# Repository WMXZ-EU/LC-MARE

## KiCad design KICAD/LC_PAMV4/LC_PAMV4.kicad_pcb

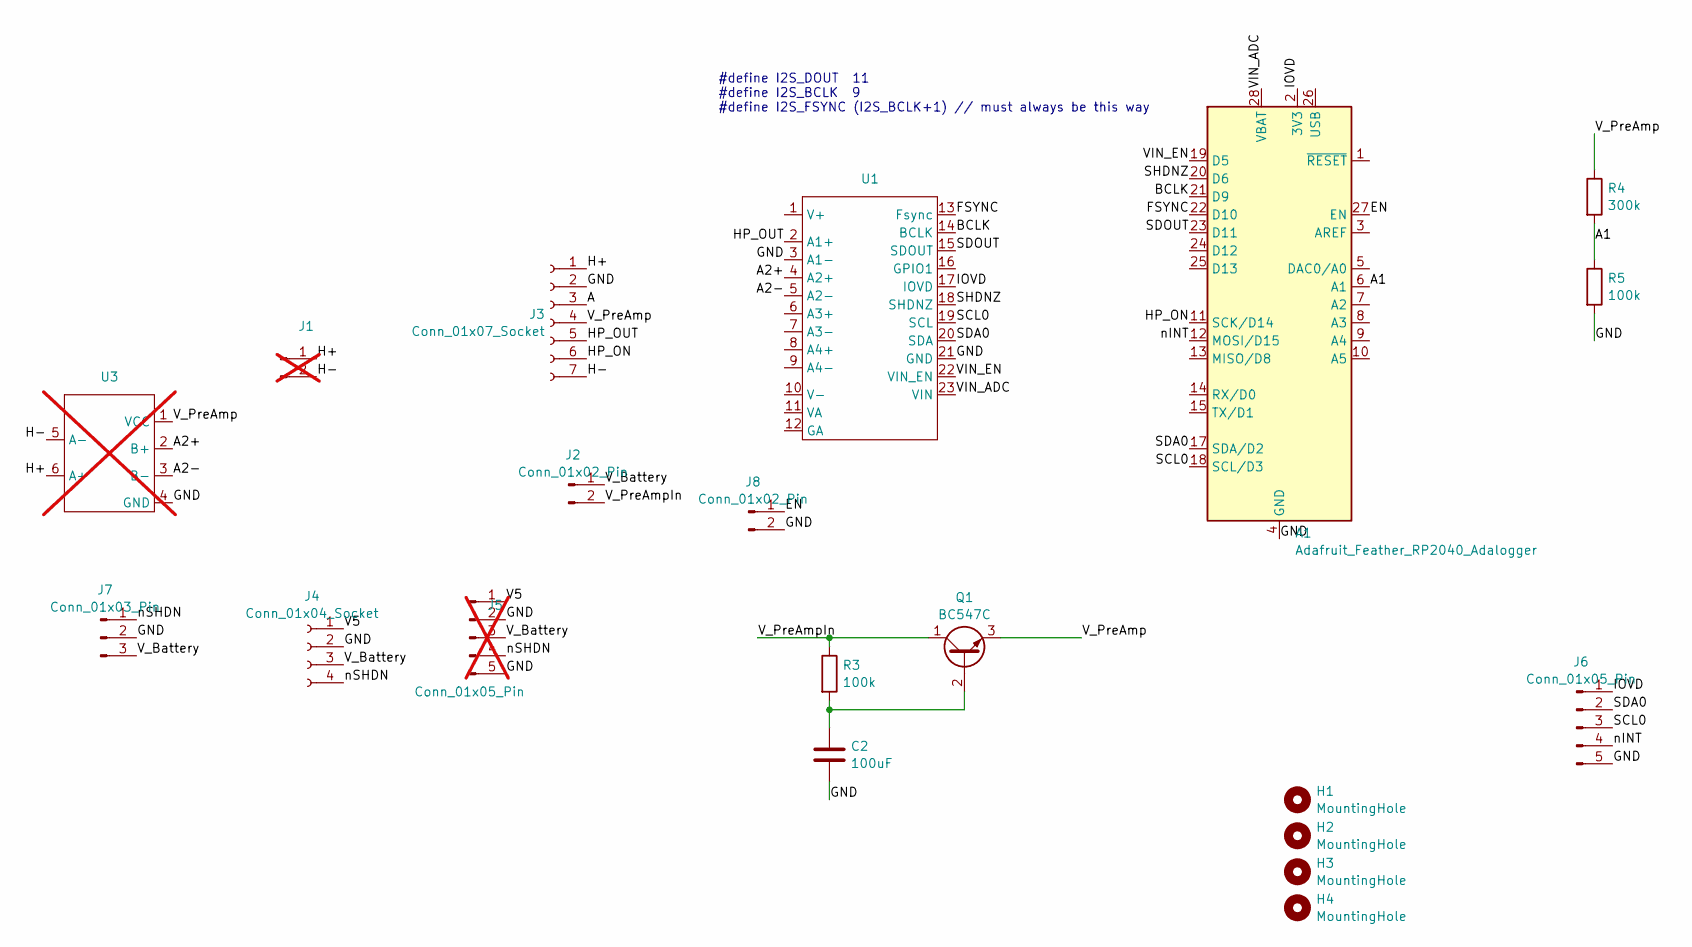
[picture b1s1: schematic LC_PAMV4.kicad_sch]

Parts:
A1: Adafruit_Feather_RP2040_Adalogger; Adafruit_Feather_WithMountingHoles
C2: 100uF; CP_Radial_D4.0mm_P2.00mm
H1, H2, H3, H4: MountingHole; MountingHole_3.2mm_M3_DIN965
J1: Conn_01x02_Male; Molex_PicoBlade_53048-0210_1x02_P1.25mm_Horizontal; not fitted
J2, J8: Conn_01x02_Pin; PinHeader_1x02_P2.54mm_Vertical
J3: Conn_01x07_Socket; HPAB
J4: Conn_01x04_Socket; PinHeader_1x04_P2.54mm_Vertical
J5: Conn_01x05_Pin; PinHeader_1x05_P2.54mm_Vertical; not fitted
J6: Conn_01x05_Pin; PinHeader_1x05_P2.54mm_Vertical
J7: Conn_01x03_Pin; PinHeader_1x03_P2.54mm_Vertical
Q1: BC547C; TO-92_Inline
R3, R5: 100k; R_Axial_DIN0204_L3.6mm_D1.6mm_P1.90mm_Vertical
R4: 300k; R_Axial_DIN0204_L3.6mm_D1.6mm_P1.90mm_Vertical
U1: ADC_V2
U3: Preamp-FET; not fitted

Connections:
/A: J3.3
/A1: A1.6 (A1), R4.2, R5.1
/A2+: U1.4 (A2+), U3.2 (B+)
/A2-: U1.5 (A2-), U3.3 (B-)
/BCLK: A1.21 (D9), U1.14 (BCLK)
/EN: A1.27 (EN), J8.1
/FSYNC: A1.22 (D10), U1.13 (Fsync)
/GND: A1.4 (GND), A1.16 (GND), C2.2, J3.2, J4.2, J5.2, J5.5, J6.5, J7.2, J8.2, R5.2, U1.3 (A1-), U1.21 (GND), U3.4 (GND)
/H+: J1.1, J3.1, U3.6 (A+)
/H-: J1.2, J3.7, U3.5 (A-)
/HP_ON: A1.11 (SCK/D24), J3.6
/HP_OUT: J3.5, U1.2 (A1+)
/IOVD: A1.2 (3V3), J6.1, U1.17 (IOVD)
/SCL0: A1.18 (SCL/D21), J6.3, U1.19 (SCL)
/SDA0: A1.17 (SDA/D20), J6.2, U1.20 (SDA)
/SDOUT: A1.23 (D11), U1.15 (SDOUT)
/SHDNZ: A1.20 (D6), U1.18 (SHDNZ)
/V5: J4.1, J5.1
/VIN_ADC: A1.28 (VBAT), U1.23 (VIN)
/VIN_EN: A1.19 (D5), U1.22 (VIN_EN)
/V_Battery: J2.1, J4.3, J5.3, J7.3
/V_PreAmp: J3.4, Q1.3 (E), R4.1, U3.1 (VCC)
/V_PreAmpIn: J2.2, Q1.1 (C), R3.1
/nINT: A1.12 (MOSI/D23), J6.4
/nSHDN: J4.4, J5.4, J7.1
unnamed: C2.1, Q1.2 (B), R3.2

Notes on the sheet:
#define I2S_DOUT 11 #define I2S_BCLK 9 #define I2S_FSYNC (I2S_BCLK+1) // must always be this way

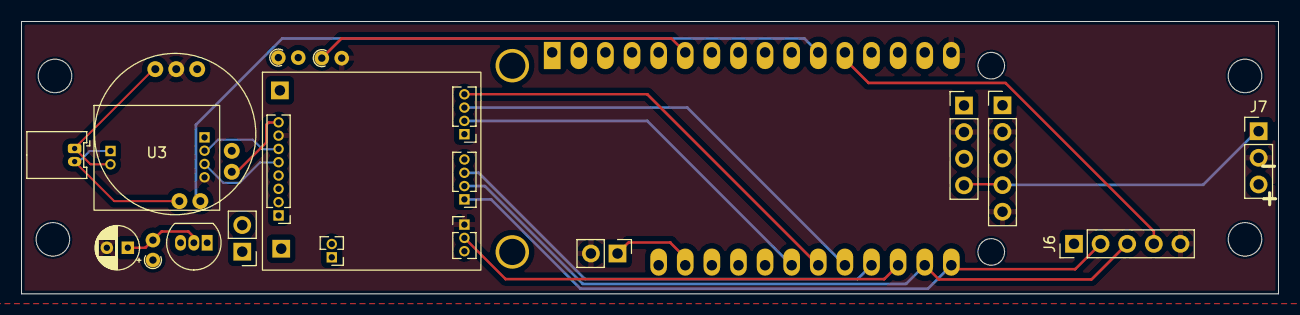
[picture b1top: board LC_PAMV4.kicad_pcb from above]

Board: 4 copper layers, 120.0 x 26.0 mm, 20 parts (1 on the bottom side), 25 nets.

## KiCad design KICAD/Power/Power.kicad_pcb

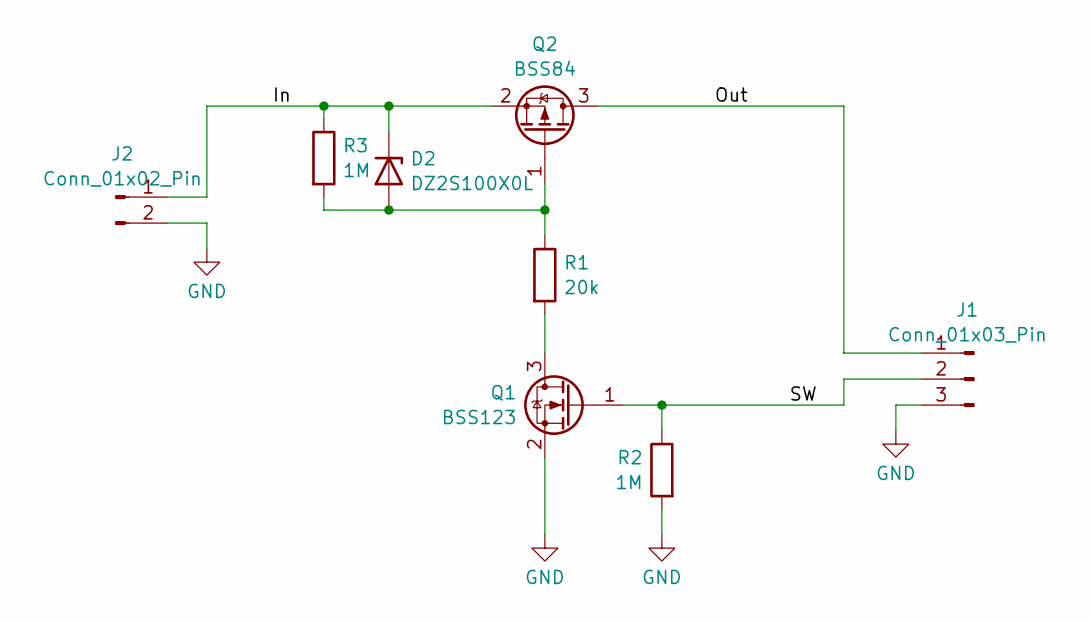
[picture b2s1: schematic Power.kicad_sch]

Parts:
D2: DZ2S100X0L; D_SOD-523
J1: Conn_01x03_Pin; PinHeader_1x03_P2.54mm_Vertical
J2: Conn_01x02_Pin; PinHeader_1x02_P2.54mm_Vertical
Q1: BSS123; SOT-23
Q2: BSS84; SOT-23
R1: 20k; R_0603_1608Metric
R2, R3: 1M; R_0603_1608Metric

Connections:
/In: D2.1 (K), J2.1, Q2.2 (S), R3.1
/Out: J1.1, Q2.3 (D)
/SW: J1.2, Q1.1 (G), R2.1
GND: J1.3, J2.2, Q1.2 (S), R2.2
unnamed: D2.2 (A), Q2.1 (G), R1.1, R3.2
unnamed: Q1.3 (D), R1.2

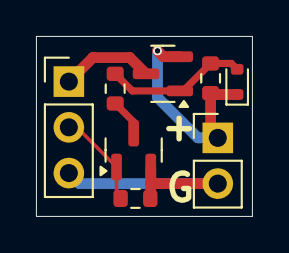
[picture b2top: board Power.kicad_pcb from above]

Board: 2 copper layers, 12.0 x 10.0 mm, 8 parts (0 on the bottom side), 6 nets.

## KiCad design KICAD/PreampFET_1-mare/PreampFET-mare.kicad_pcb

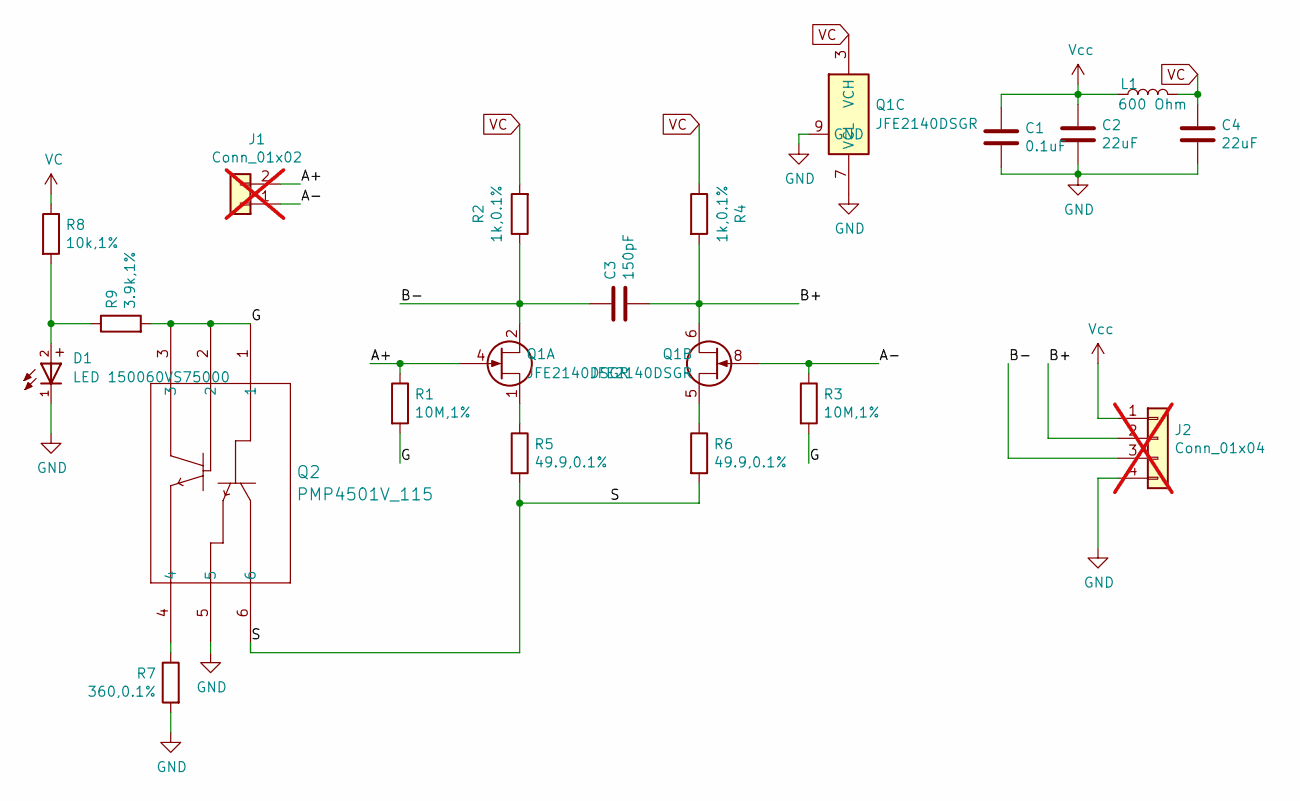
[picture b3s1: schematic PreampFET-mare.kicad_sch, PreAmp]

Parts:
C1: 0.1uF; C_0402_1005Metric
C2, C4: 22uF; C_0603_1608Metric
C3: 150pF; C_0402_1005Metric
D1: LED 150060VS75000; WL-SMCW_0603
J1: Conn_01x02; PinHeader_1x02_P1.27mm_Vertical; not fitted
J2: Conn_01x04; PinHeader_1x04_P1.27mm_Vertical; not fitted
L1: 600 Ohm; L_0603_1608Metric
Q1: JFE2140DSGR; WSON-8-1EP_2x2mm_P0.5mm_EP0.9x1.6mm_ThermalVias
Q2: PMP4501V_115; SOT666_NEX
R1, R3: 10M,1%; R_0402_1005Metric
R2, R4: 1k,0.1%; R_0402_1005Metric
R5, R6: 49.9,0.1%; R_0402_1005Metric
R7: 360,0.1%; R_0402_1005Metric
R8: 10k,1%; R_0402_1005Metric
R9: 3.9k,1%; R_0402_1005Metric

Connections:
/A+: J1.2, Q1.4, R1.1
/A-: J1.1, Q1.8, R3.1
/B+: C3.2, J2.2, Q1.6, R4.2
/B-: C3.1, J2.3, Q1.2, R2.1
/G: Q2.1, Q2.2, Q2.3, R1.2, R3.2, R9.2
/S: Q2.6, R5.2, R6.2
GND: C1.2, C2.2, C4.2, D1.1, J2.4, Q1.7 (VCL), Q1.9 (GND), Q2.5, R7.2
unnamed: D1.2, R8.2, R9.1
unnamed: Q1.1, R5.1
unnamed: Q1.5, R6.1
unnamed: Q2.4, R7.1
VC: C4.1, L1.2, Q1.3 (VCH), R2.2, R4.1, R8.1
Vcc: C1.1, C2.1, J2.1, L1.1

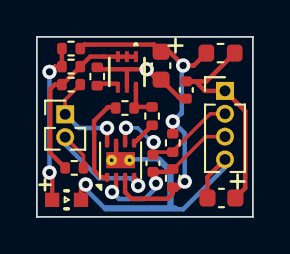
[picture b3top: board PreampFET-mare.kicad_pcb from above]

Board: 2 copper layers, 12.0 x 10.0 mm, 19 parts (0 on the bottom side), 13 nets.

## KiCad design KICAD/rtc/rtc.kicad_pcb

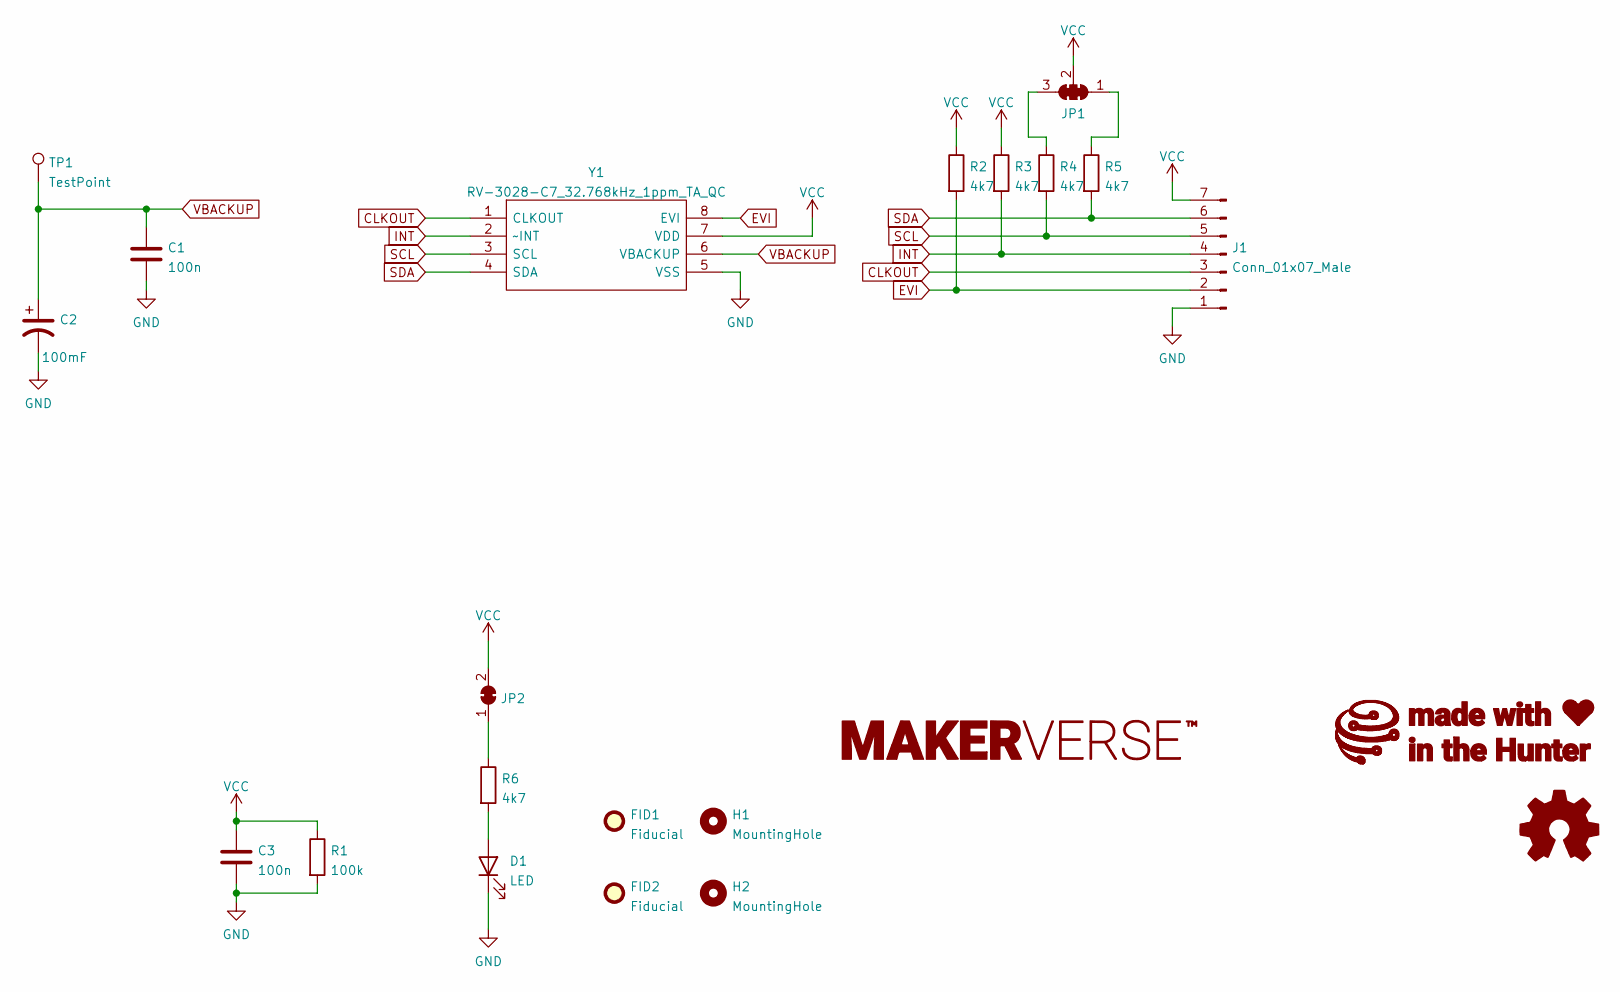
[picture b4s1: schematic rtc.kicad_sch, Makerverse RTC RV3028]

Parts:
C1, C3: 100n; C_0402_1005Metric
C2: 100mF; FC_10.5X5.5_
D1: LED; LED_0603_1608Metric
FID1, FID2: Fiducial; Fiducial_1mm_Mask2mm
H1, H2: MountingHole; MountingHole_3.2mm_M3
J1: Conn_01x07_Male; PinSocket_1x07_P2.54mm_Vertical
JP1: SolderJumper_3_Bridged123; SolderJumper-3_P1.3mm_Closed_RoundedPad1.0x1.5mm
JP2: SolderJumper_2_Bridged; SolderJumper-2_P1.3mm_Bridged_RoundedPad1.0x1.5mm
R1: 100k; R_0402_1005Metric
R2, R3, R4, R5, R6: 4k7; R_0402_1005Metric
TP1: TestPoint; TestPoint_THTPad_D1.5mm_Drill0.7mm
Y1: RV-3028-C7_32.768kHz_1ppm_TA_QC; RV3028C732768kHz1ppmTAQC; Mouser Part Number 428-203591-MG01

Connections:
CLKOUT: J1.3, Y1.1 (CLKOUT)
EVI: J1.2, R2.2, Y1.8 (EVI)
GND: C1.2, C2.2, C3.2, D1.1 (K), J1.1, R1.2, Y1.5 (VSS)
INT: J1.4, R3.2, Y1.2 (~INT)
unnamed: D1.2 (A), R6.2
unnamed: JP1.1 (A), R5.1
unnamed: JP1.3 (B), R4.1
unnamed: JP2.1 (A), R6.1
SCL: J1.5, R4.2, Y1.3 (SCL)
SDA: J1.6, R5.2, Y1.4 (SDA)
VBACKUP: C1.1, C2.1, TP1.1, Y1.6 (VBACKUP)
VCC: C3.1, J1.7, JP1.2 (C), JP2.2 (B), R1.1, R2.1, R3.1, Y1.7 (VDD)

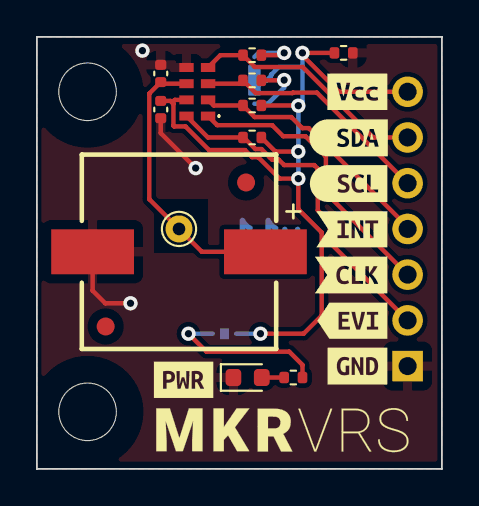
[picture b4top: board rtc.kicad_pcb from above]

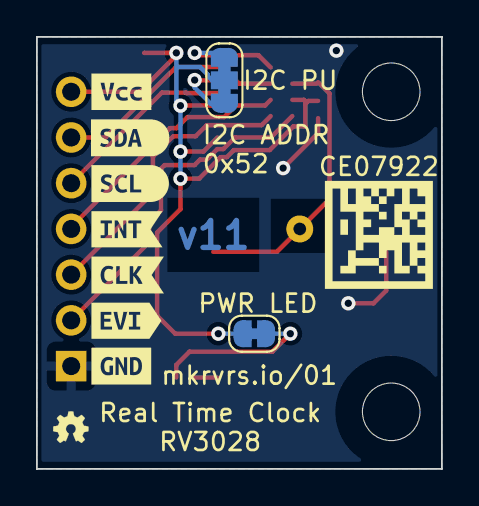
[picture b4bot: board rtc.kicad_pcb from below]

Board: 2 copper layers, 22.5 x 24.0 mm, 35 parts (9 on the bottom side), 12 nets.

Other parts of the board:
G1: LOGO; makerverse_logo_short_14.0x2.4mm
kibuzzard-610A0DD3: G***; kibuzzard-610A0DD3
kibuzzard-611F2ECA: G***; kibuzzard-611F2ECA
kibuzzard-611F2EE3: G***; kibuzzard-611F2EE3
kibuzzard-611F2EF5: G***; kibuzzard-611F2EF5
kibuzzard-611F2F08: G***; kibuzzard-611F2F08
kibuzzard-611F2F8F: G***; kibuzzard-611F2F8F
kibuzzard-611F2F9E: G***; kibuzzard-611F2F9E
kibuzzard-611F2FAD: G***; kibuzzard-611F2FAD
kibuzzard-611F2FF6: G***; kibuzzard-611F2FF6
kibuzzard-611F3003: G***; kibuzzard-611F3003
kibuzzard-611F3011: G***; kibuzzard-611F3011
kibuzzard-6109FC7A, kibuzzard-6109FC7A#2: G***; kibuzzard-6109FC7A
kibuzzard-6109FD62, kibuzzard-6109FD62#2: G***; kibuzzard-6109FD62

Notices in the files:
KICAD/rtc/rtc.kicad_pcb:
License: CCASAv4.0 https://creativecommons.org/licenses/by-sa/4.0
